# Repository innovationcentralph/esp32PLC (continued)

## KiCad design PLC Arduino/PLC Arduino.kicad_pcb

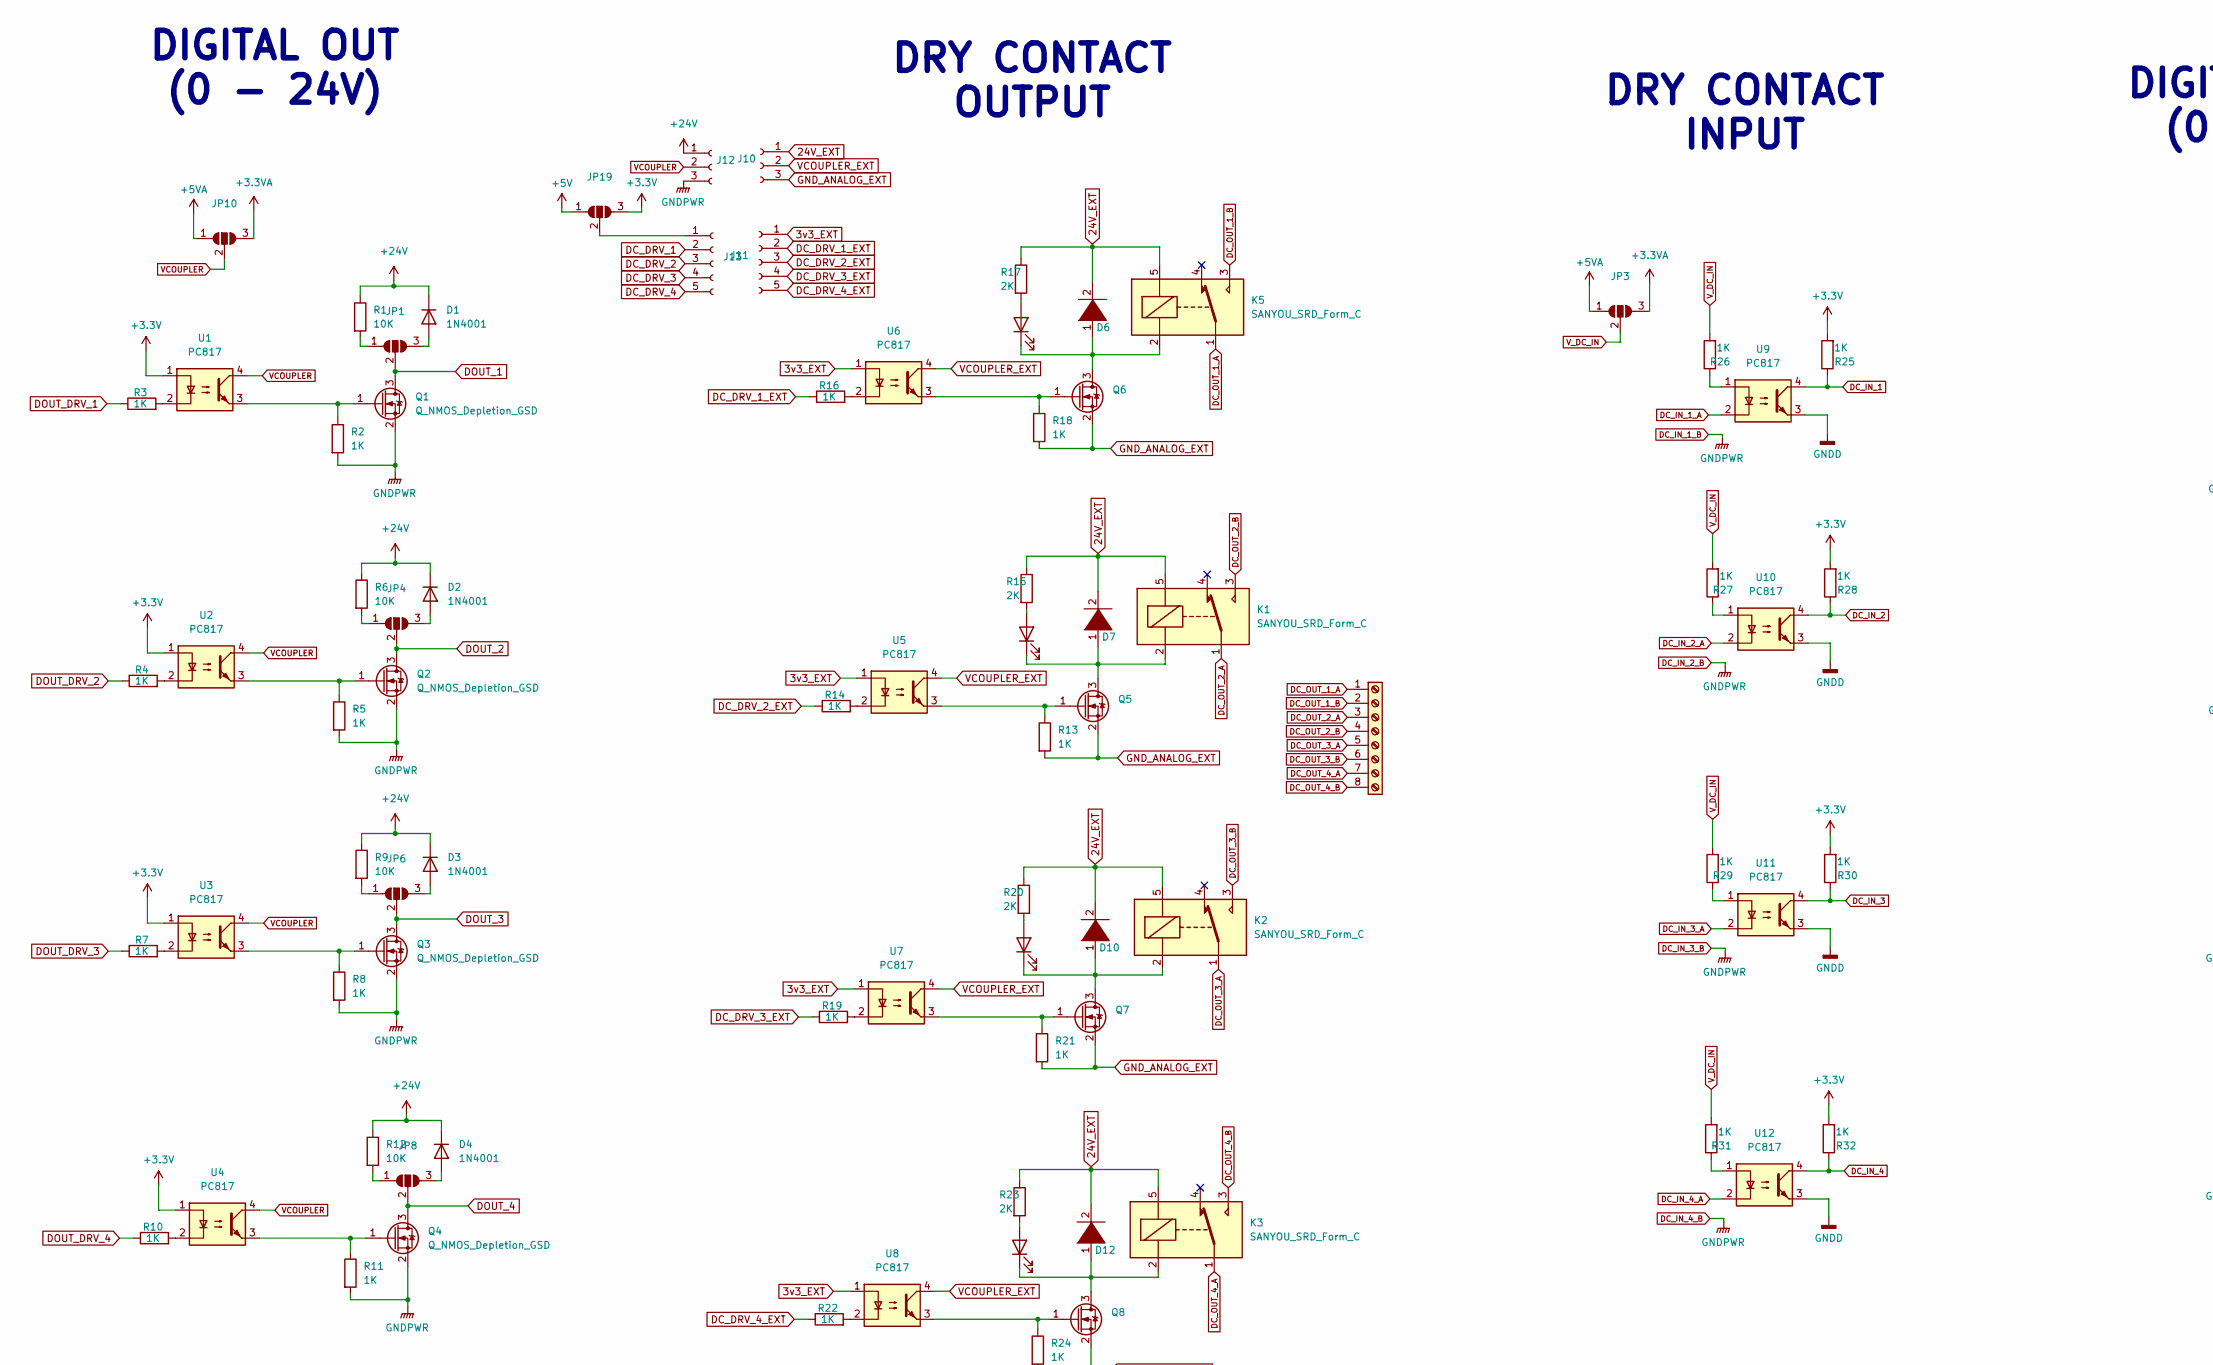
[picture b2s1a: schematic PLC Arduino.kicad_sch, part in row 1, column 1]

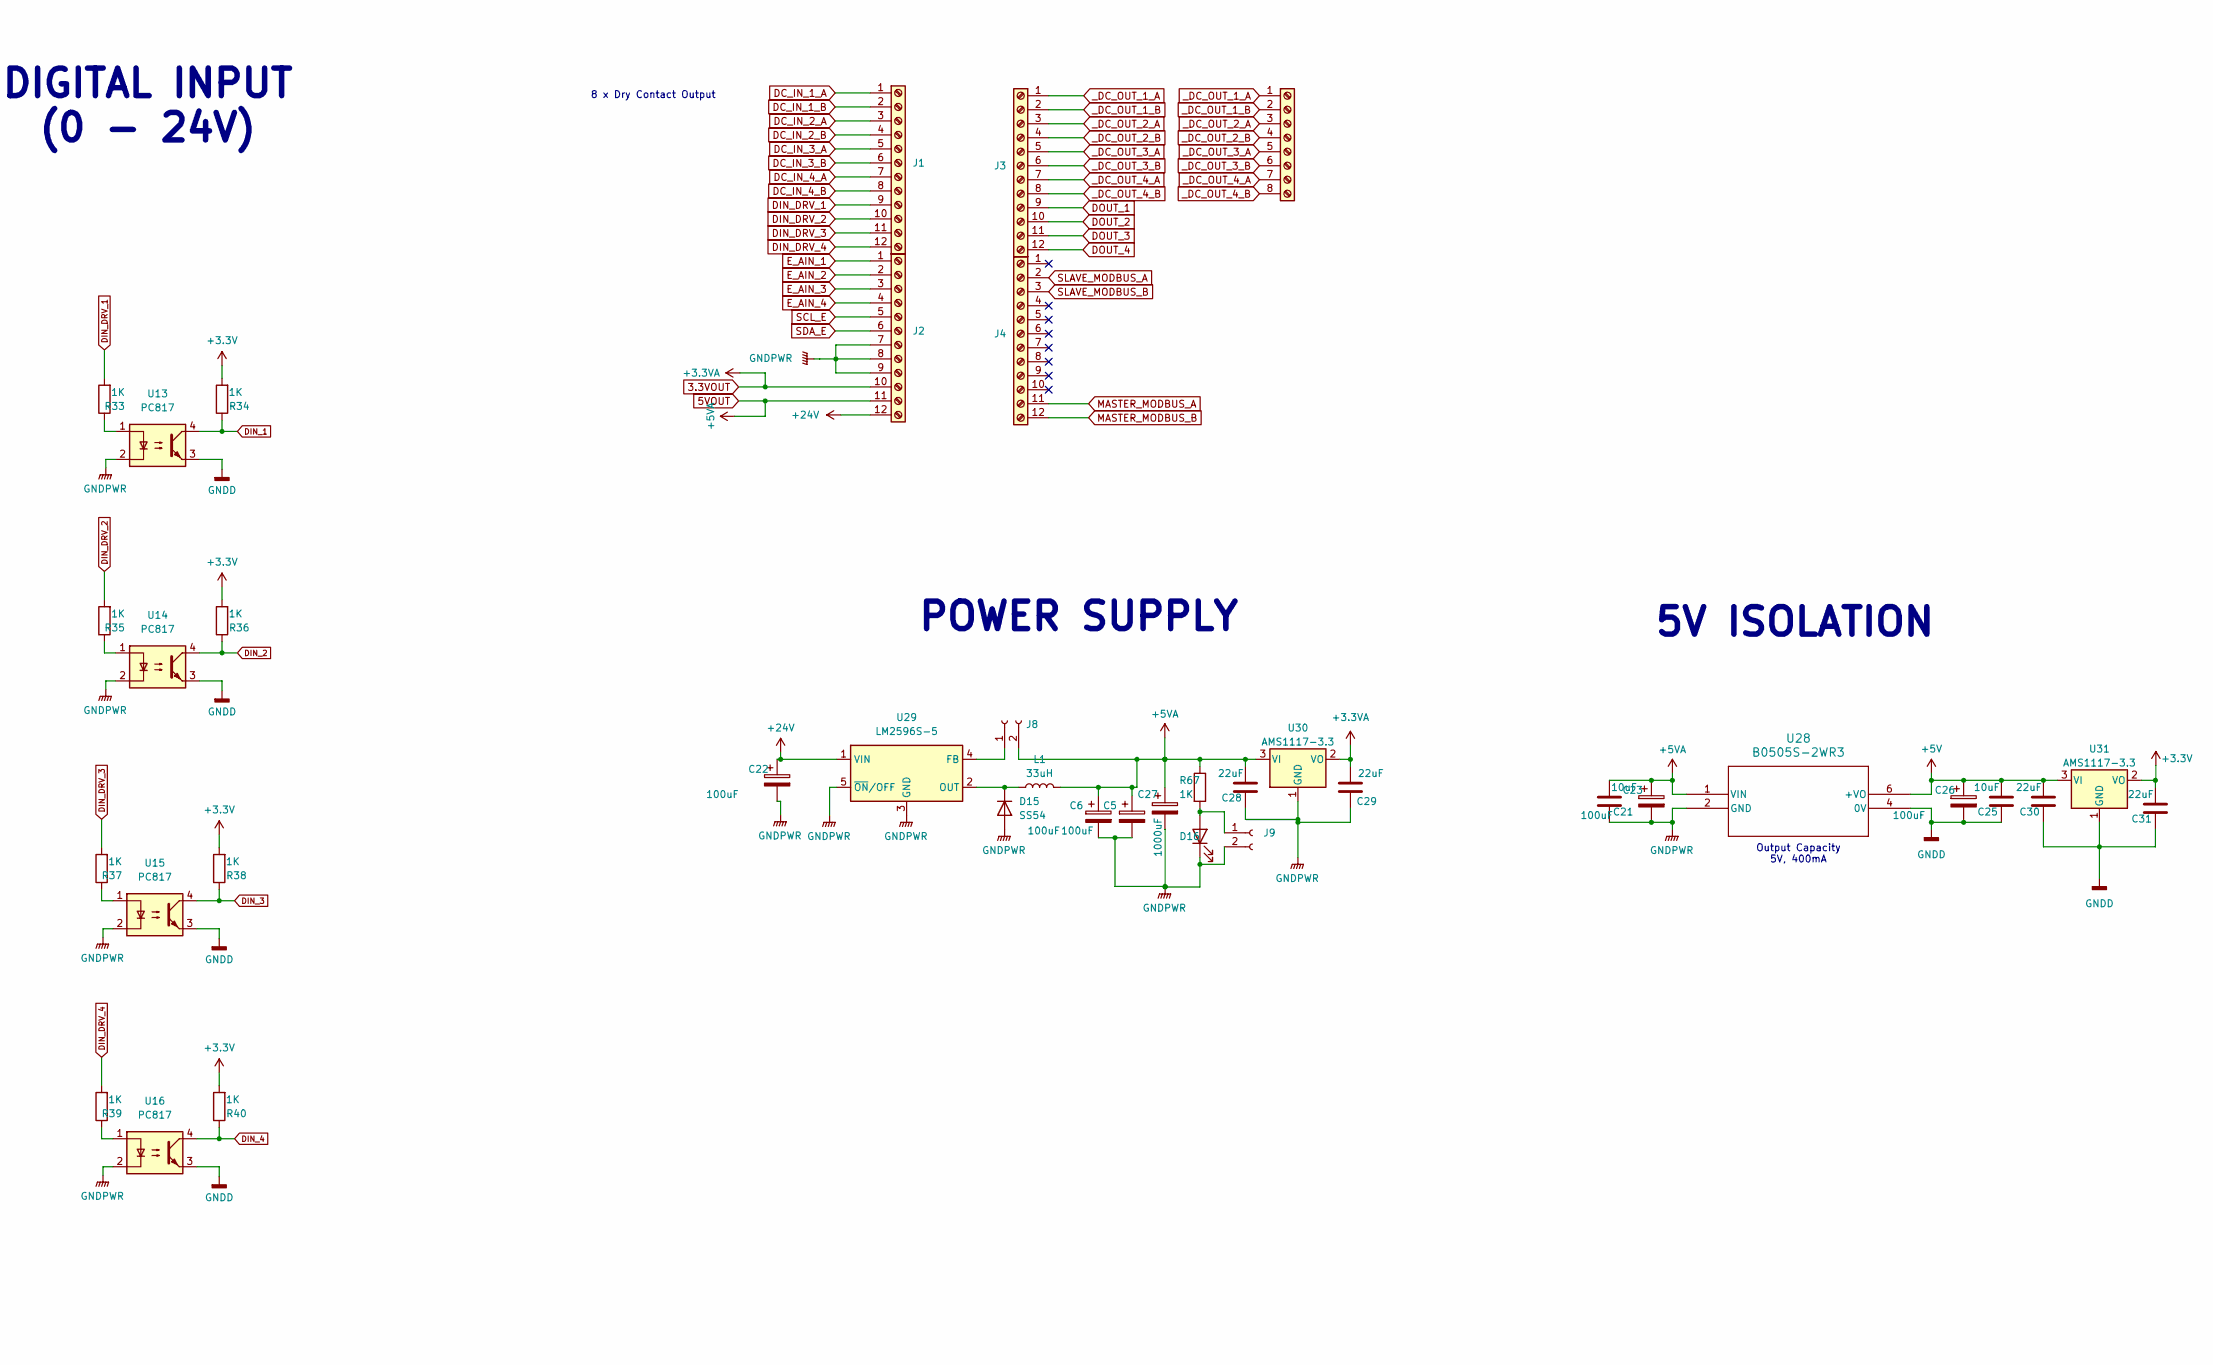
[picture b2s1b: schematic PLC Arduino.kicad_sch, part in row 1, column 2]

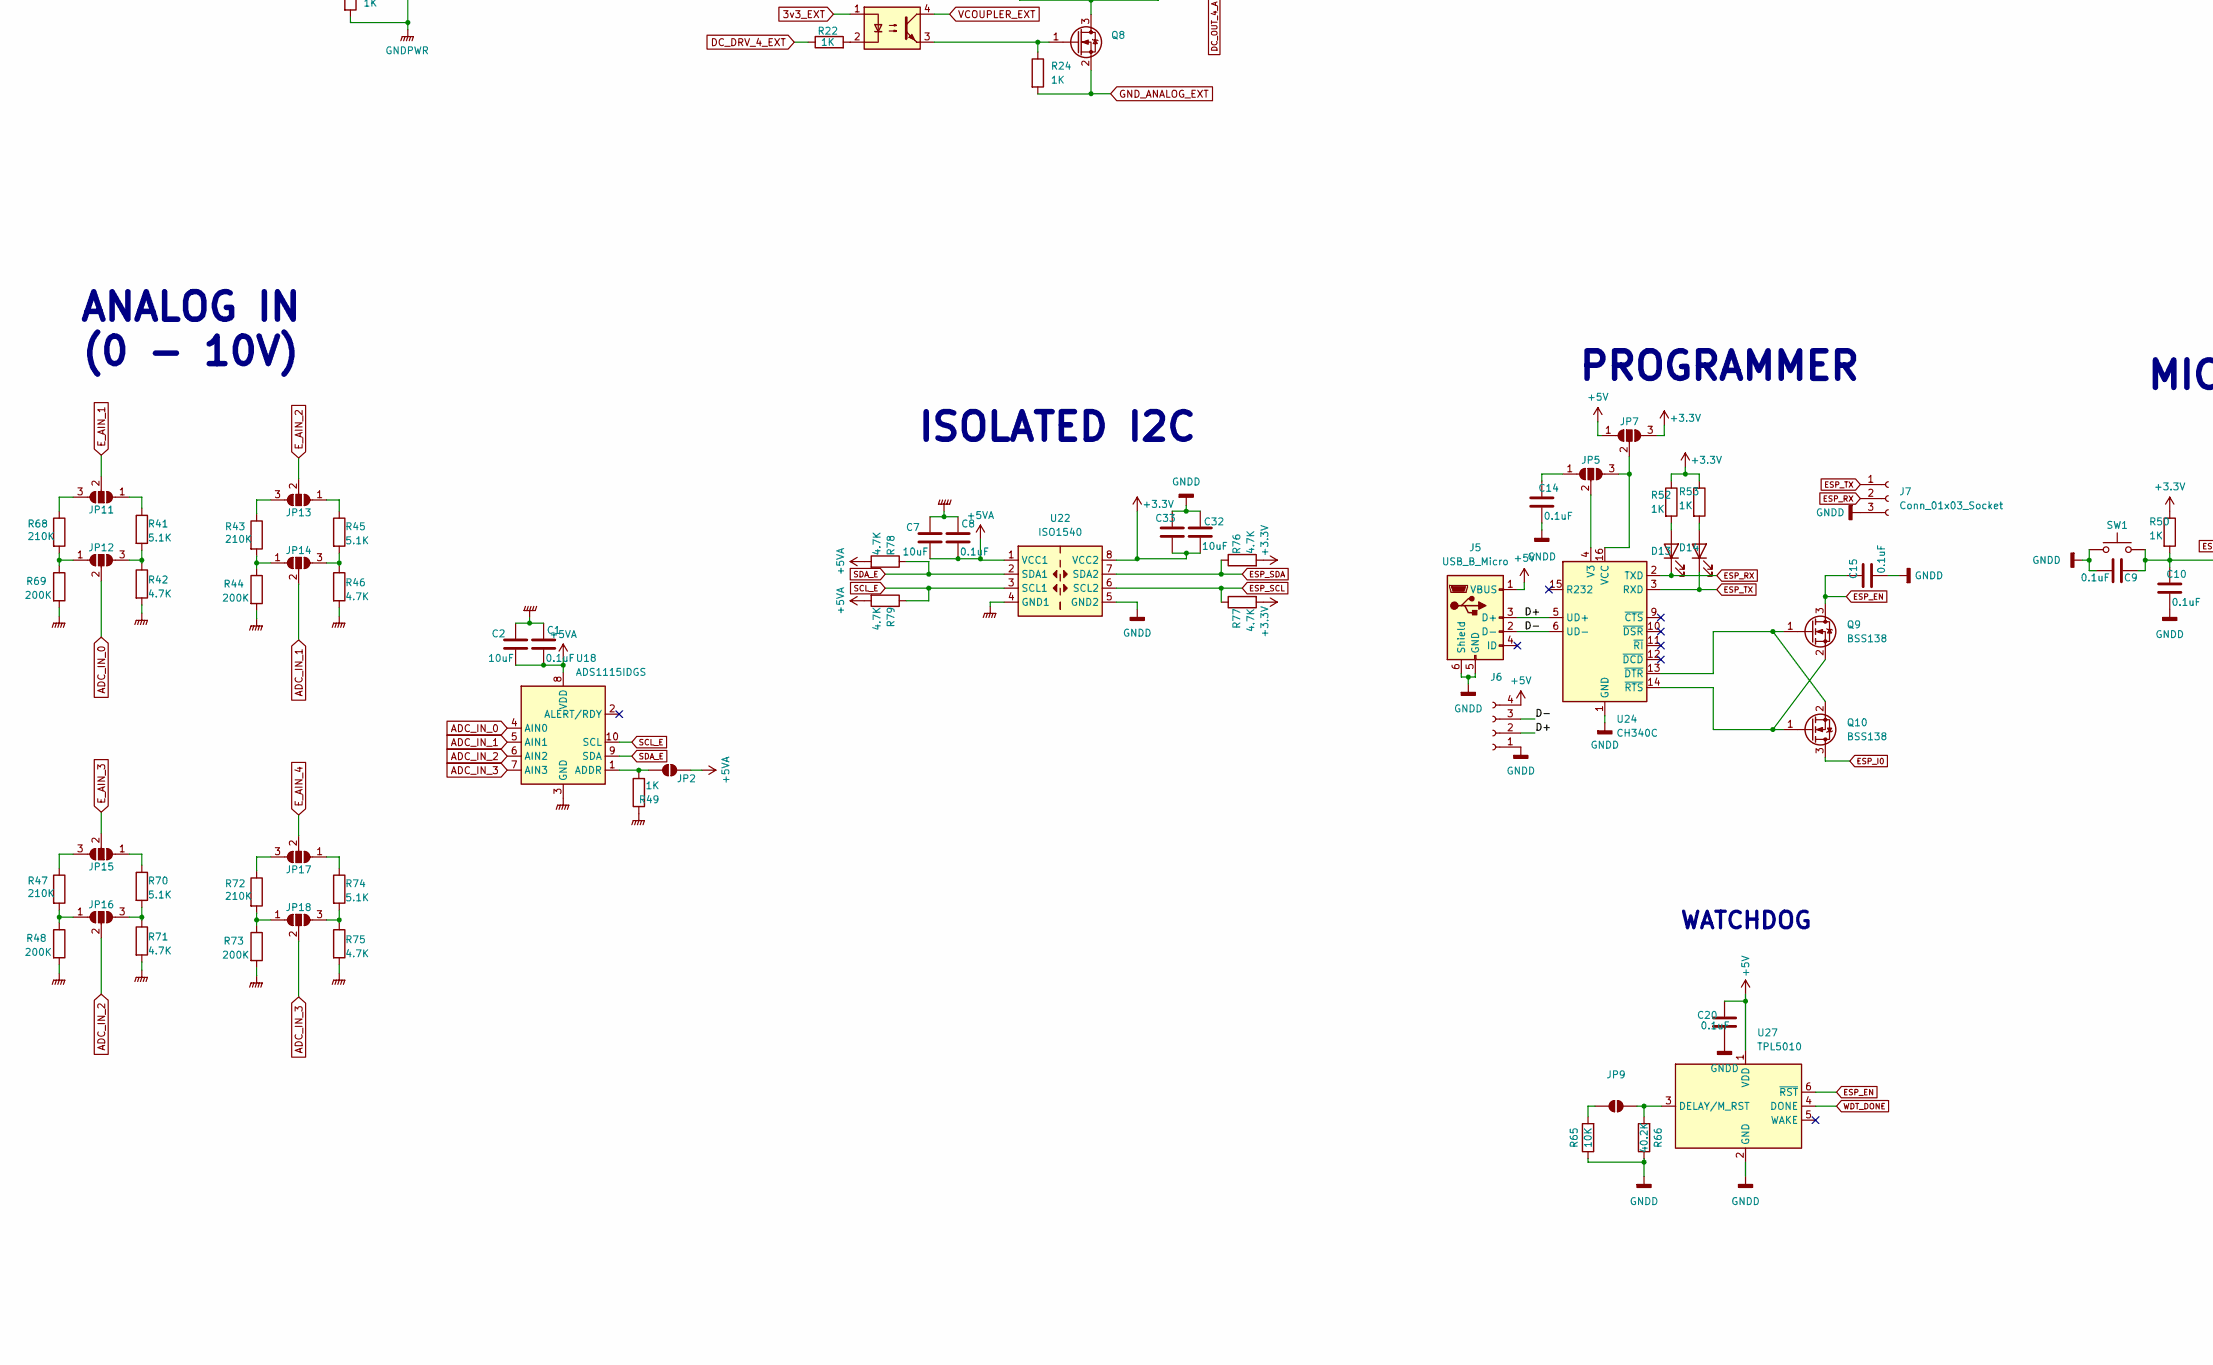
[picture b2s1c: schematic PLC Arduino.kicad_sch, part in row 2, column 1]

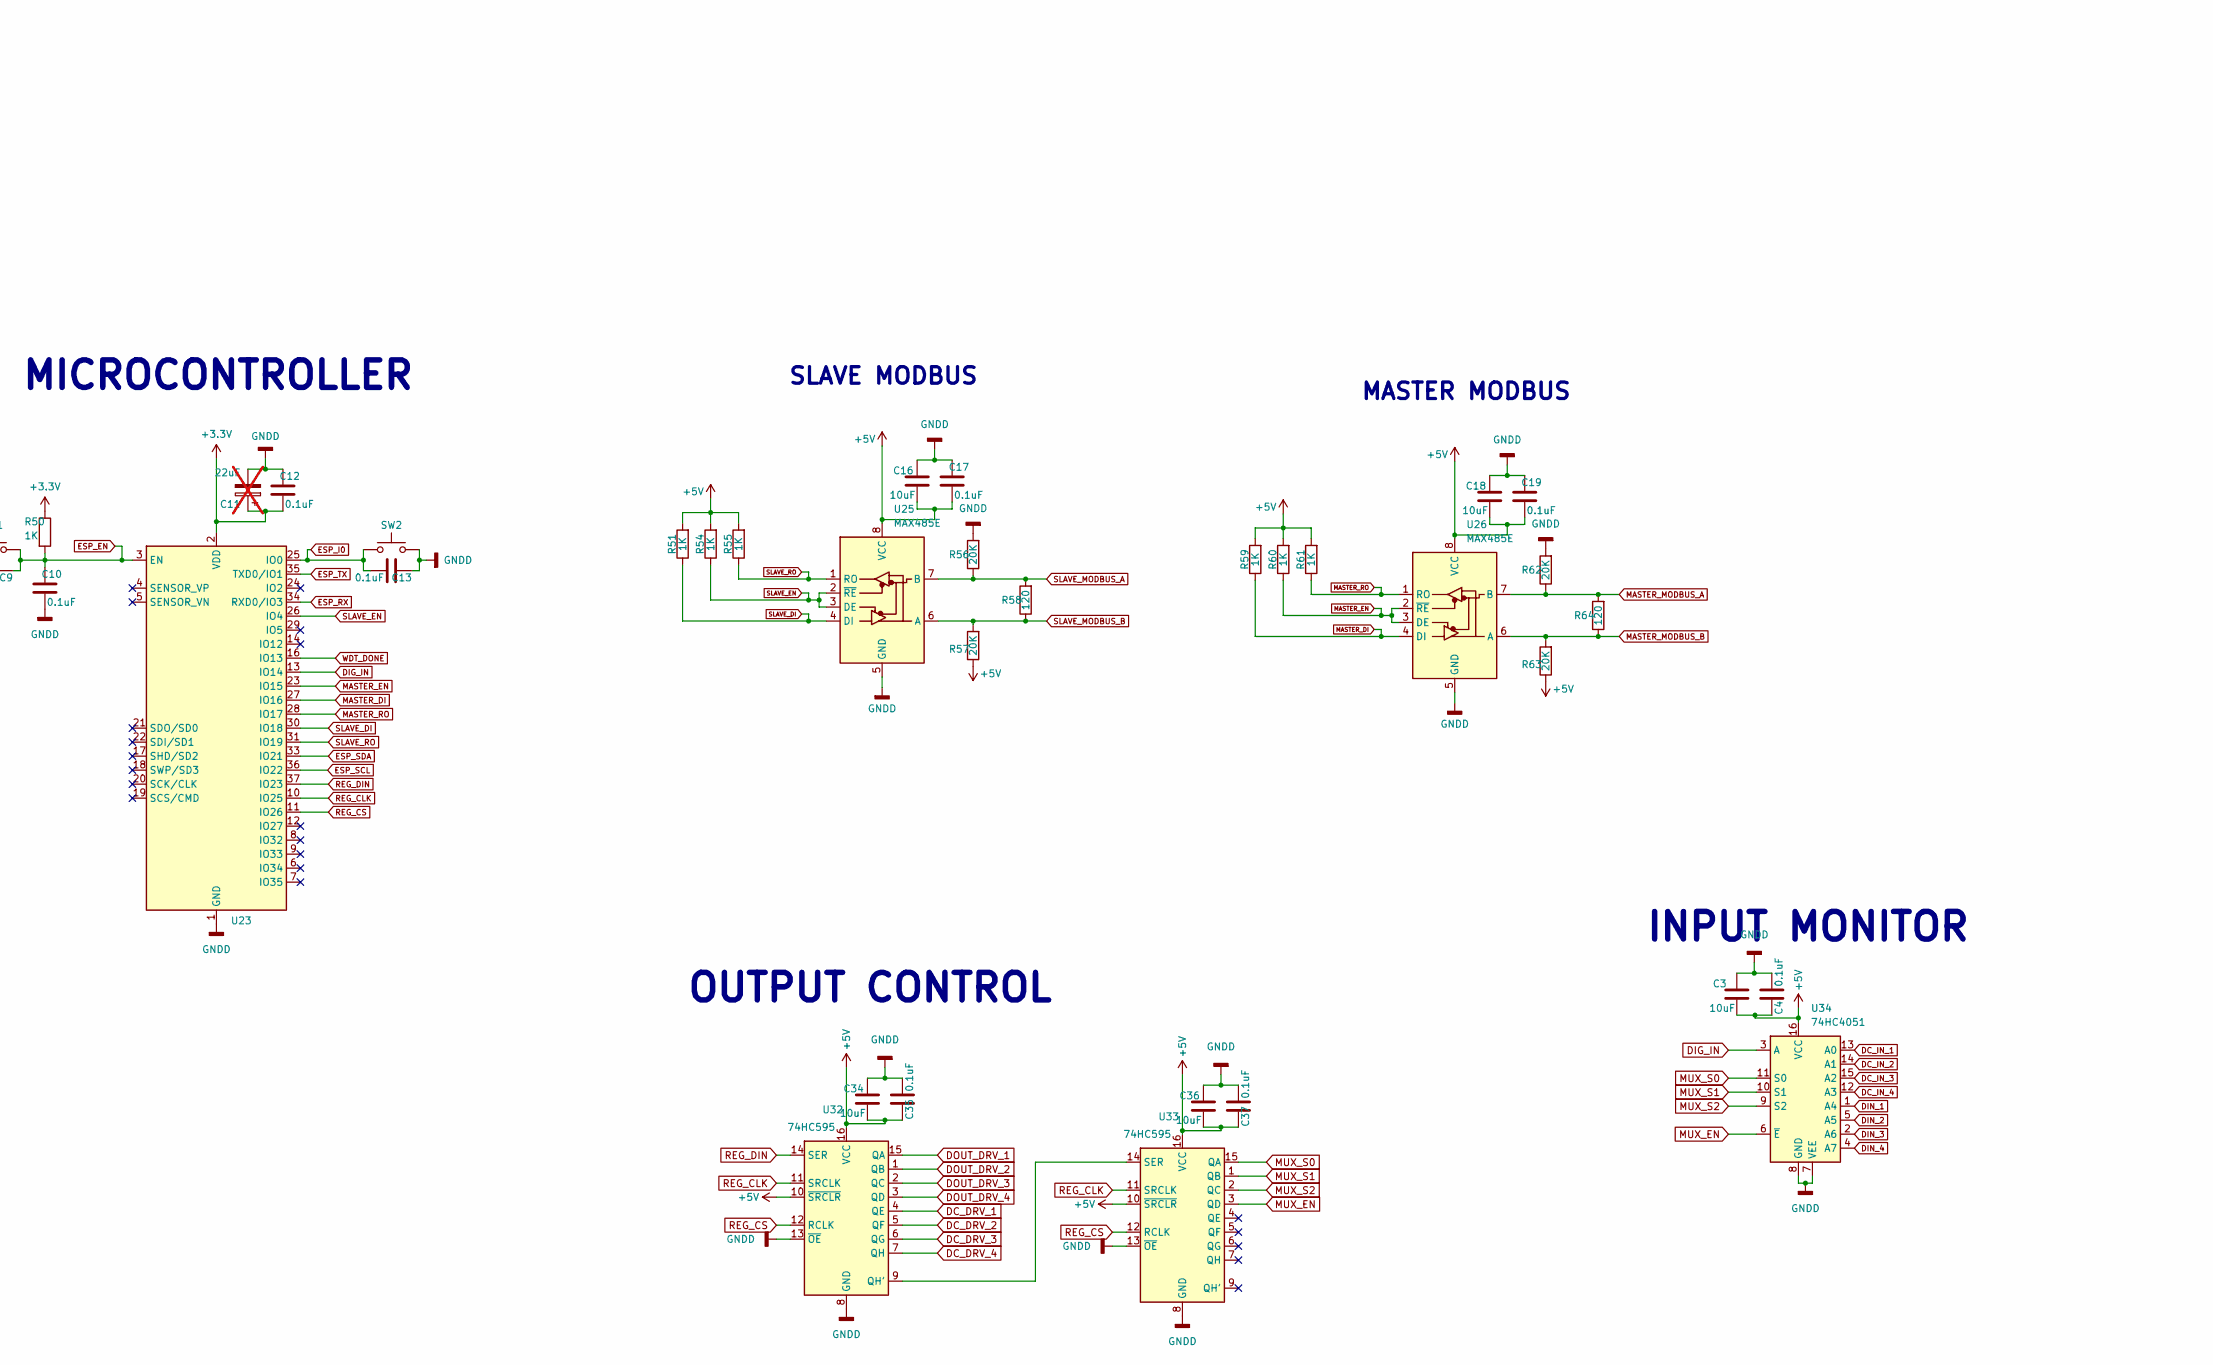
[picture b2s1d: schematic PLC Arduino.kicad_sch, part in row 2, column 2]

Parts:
C1, C4, C8, C9, C10, C12, C13, C14, C15, C17, C19, C20, C33, C35, C37: 0.1uF; C_0402_1005Metric; LCSC C60474
C2, C3, C7, C16, C18, C21, C25, C32, C34, C36: 10uF; C_0805_2012Metric_Pad1.18x1.45mm_HandSolder; LCSC C15850
C5, C6, C23, C26: 100uF; C_1210_3225Metric_Pad1.33x2.70mm_HandSolder; LCSC C394395
C11: 22uF; C_0603_1608Metric; LCSC C59461; not fitted
C22: 100uF; C_Elec_10x10.2; LCSC C28241
C27: 1000uF; C_Elec_10x10.2; LCSC C189257
C28, C29, C30, C31: 22uF; C_0603_1608Metric; LCSC C59461
D1, D2, D3, D4, D6, D7, D10, D12: 1N4001; D_SOD-123F; LCSC C2892326
D5, D8, D9, D11, D13, D14, D16: LED; LED_0805_2012Metric_Pad1.15x1.40mm_HandSolder; LCSC C2297
D15: SS54; D_SMA; LCSC C22452
J1, J2, J3, J4: Screw_Terminal_01x12; TerminalBlock_Phoenix_MKDS-1,5-12-5.08_1x12_P5.08mm_Horizon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
J5: USB_B_Micro; USB_Micro-B_Molex-105017-0001; LCSC C2972784
J6: Conn_01x04_Socket; JST_EH_B4B-EH-A_1x04_P2.50mm_Vertical
J7: Conn_01x03_Socket; JST_EH_B3B-EH-A_1x03_P2.50mm_Vertical
J8: Conn_01x02_Socket; PinHeader_1x02_P2.54mm_Vertical
J9: Conn_01x02_Socket; JST_EH_B2B-EH-A_1x02_P2.50mm_Vertical
J10, J12: Conn_01x03_Socket; PinHeader_1x03_P2.54mm_Vertical
J11, J13: Conn_01x05_Socket; PinHeader_1x05_P2.54mm_Vertical
J14, J15: Screw_Terminal_01x08; TerminalBlock_bornier-8_P5.08mm
JP1, JP3, JP4, JP5, JP6, JP7, JP8, JP10, JP11, JP12, JP13, JP14, JP15, JP16, JP17, JP18, JP19: SolderJumper_3_Open; SolderJumper-3_P1.3mm_Open_Pad1.0x1.5mm
JP2, JP9: SolderJumper_2_Open; SolderJumper-2_P1.3mm_Open_Pad1.0x1.5mm
K1, K2, K3, K5: SANYOU_SRD_Form_C; Relay_SPDT_SANYOU_SRD_Series_Form_C; LCSC C15840
L1: 33uH; L_Chilisin_BMRF00101040; LCSC C408490
Q1, Q2, Q3, Q4, Q5, Q6, Q7, Q8: Q_NMOS_Depletion_GSD; SOT-23-3; LCSC C75882
Q9, Q10: BSS138; SOT-23; LCSC C426569
R1, R6, R9, R12, R65: 10K; R_0603_1608Metric_Pad0.98x0.95mm_HandSolder; LCSC C25804
R2, R3, R4, R5, R7, R8, R10, R11, R13, R14, R16, R18, R19, R21, R22, R24, R25, R26, R27, R28, R29, R30, R31, R32, R33, R34, R35, R36, R37, R38, R39, R40, R49, R50, R51, R52, R53, R54, R55, R59, R60, R61, R67: 1K; R_0603_1608Metric_Pad0.98x0.95mm_HandSolder; LCSC C21190
R15, R17, R20, R23: 2K; R_0603_1608Metric_Pad0.98x0.95mm_HandSolder; LCSC C22975
R41, R45, R70, R74: 5.1K; R_0402_1005Metric_Pad0.72x0.64mm_HandSolder; LCSC C25905
R42, R46, R71, R75, R76, R77, R78, R79: 4.7K; R_0402_1005Metric_Pad0.72x0.64mm_HandSolder; LCSC C25900
R43, R47, R68, R72: 210K; R_0402_1005Metric_Pad0.72x0.64mm_HandSolder; LCSC C2686484
R44, R48, R69, R73: 200K; R_0402_1005Metric_Pad0.72x0.64mm_HandSolder; LCSC C286555
R56, R57, R62, R63: 20K; R_0805_2012Metric_Pad1.20x1.40mm_HandSolder; LCSC C163978
R58, R64: 120; R_0805_2012Metric_Pad1.20x1.40mm_HandSolder; LCSC C2907224
R66: 40.2K; R_0603_1608Metric_Pad0.98x0.95mm_HandSolder; LCSC C12447
SW1, SW2: SW_Push; SW_SPST_CK_RS282G05A3; LCSC C2689642
U1, U2, U3, U4, U5, U6, U7, U8, U9, U10, U11, U12, U13, U14, U15, U16: PC817; APC-817xx-SL_AMB; LCSC C66405
U18: ADS1115IDGS; DGS0010A_L; LCSC C37593
U22: ISO1540; SOIC-8_3.9x4.9mm_P1.27mm; LCSC C179739
U23: ESP32-WROOM-32; LCSC C529577
U24: CH340C; SOP-16_3.9x9.9mm_P1.27mm; LCSC C84681
U25, U26: MAX485E; SOP-8_3.9x4.9mm_P1.27mm; LCSC C481667
U27: TPL5010; SOT-23-6; LCSC C473912
U28: B0505S-2WR3; B_S-2WR2_MNS; LCSC C5369473
U29: LM2596S-5; TO-263-5_TabPin3; LCSC C347421
U30, U31: AMS1117-3.3; SOT-223-3_TabPin2; LCSC C5199435
U32, U33: 74HC595; SOIC-16_3.9x9.9mm_P1.27mm; LCSC C5947
U34: 74HC4051; SO-16_3.9x9.9mm_P1.27mm; LCSC C9386

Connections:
3.3VOUT: C29.2, J2.10, JP3.3 (B), JP10.3 (B), U30.2 (VO)
3v3_EXT: J11.1, U5.1, U6.1, U7.1, U8.1
5VOUT: C1.1, C2.2, C5.1, C6.1, C7.2, C8.1, C21.2, C23.1, C27.1, C28.2, J2.11, J8.2, JP2.2 (B), JP3.1 (A), JP10.1 (A), L1.2, R67.1, R78.2, R79.2, U18.8 (VDD), U22.1 (VCC1), U28.1 (VIN), U30.3 (VI)
24V_EXT: D6.2 (A), D7.2 (A), D10.2 (A), D12.2 (A), J10.1, K1.5, K2.5, K3.5, K5.5, R15.1, R17.1, R20.1, R23.1
+3.3V: C11.1, C12.1, C31.2, C32.2, C33.1, JP7.3 (B), JP19.3 (B), R25.2, R28.2, R30.2, R32.2, R34.2, R36.2, R38.2, R40.2, R50.1, R52.1, R53.1, R76.2, R77.2, U1.1, U2.1, U3.1, U4.1, U22.8 (VCC2), U23.2 (VDD), U31.2 (VO)
+5V: C3.2, C4.2, C16.2, C17.1, C18.2, C19.1, C20.1, C25.2, C26.1, C30.2, C34.2, C35.2, C36.2, C37.2, J5.1 (VBUS), J6.4, JP7.1 (A), JP19.1 (A), R51.2, R54.2, R55.2, R57.1, R59.2, R60.2, R61.2, R63.1, U25.8 (VCC), U26.8 (VCC), U27.1 (VDD), U28.6 (+VO), U31.3 (VI), U32.10 (~SRCLR), U32.16 (VCC), U33.10 (~SRCLR), U33.16 (VCC), U34.16 (VCC)
+24V: C22.1, D1.1 (K), D2.1 (K), D3.1 (K), D4.1 (K), J2.12, J12.1, R1.1, R6.1, R9.1, R12.1, U29.1 (VIN)
/D+: J5.3 (D+), J6.2, U24.5 (UD+)
/D-: J5.2 (D-), J6.3, U24.6 (UD-)
ADC_IN_0: JP12.2 (C), U18.4 (AIN0)
ADC_IN_1: JP14.2 (C), U18.5 (AIN1)
ADC_IN_2: JP16.2 (C), U18.6 (AIN2)
ADC_IN_3: JP18.2 (C), U18.7 (AIN3)
DC_DRV_1: J13.2, U32.4 (QE)
DC_DRV_1_EXT: J11.2, R16.1
DC_DRV_2: J13.3, U32.5 (QF)
DC_DRV_2_EXT: J11.3, R14.1
DC_DRV_3: J13.4, U32.6 (QG)
DC_DRV_3_EXT: J11.4, R19.1
DC_DRV_4: J13.5, U32.7 (QH)
DC_DRV_4_EXT: J11.5, R22.1
DC_IN_1: R25.1, U9.4, U34.13 (A0)
DC_IN_1_A: J1.1, U9.2
DC_IN_1_B: C1.2, C2.1, C5.2, C6.2, C7.1, C8.2, C21.1, C22.2, C23.2, C27.2, C28.1, C29.1, D15.2 (A), D16.1 (K), J1.2, J1.4, J1.6, J1.8, J2.7, J2.8, J2.9, J9.2, J12.3, Q1.2 (S), Q2.2 (S), Q3.2 (S), Q4.2 (S), R2.2, R5.2, R8.2, R11.2, R42.2, R44.2, R46.2, R48.2, R49.1, R69.2, R71.2, R73.2, R75.2, U13.2, U14.2, U15.2, U16.2, U18.3 (GND), U22.4 (GND1), U28.2 (GND), U29.3 (GND), U29.5 (~ON/OFF), U30.1 (GND)
DC_IN_2: R28.1, U10.4, U34.14 (A1)
DC_IN_2_A: J1.3, U10.2
DC_IN_3: R30.1, U11.4, U34.15 (A2)
DC_IN_3_A: J1.5, U11.2
DC_IN_4: R32.1, U12.4, U34.12 (A3)
DC_IN_4_A: J1.7, U12.2
DC_OUT_1_A: J14.1, K5.1
DC_OUT_1_B: J14.2, K5.3
DC_OUT_2_A: J14.3, K1.1
DC_OUT_2_B: J14.4, K1.3
DC_OUT_3_A: J14.5, K2.1
DC_OUT_3_B: J14.6, K2.3
DC_OUT_4_A: J14.7, K3.1
DC_OUT_4_B: J14.8, K3.3
DIG_IN: U23.13 (IO14), U34.3 (A)
DIN_1: R34.1, U13.4, U34.1 (A4)
DIN_2: R36.1, U14.4, U34.5 (A5)
DIN_3: R38.1, U15.4, U34.2 (A6)
DIN_4: R40.1, U16.4, U34.4 (A7)
DIN_DRV_1: J1.9, R33.2
DIN_DRV_2: J1.10, R35.2
DIN_DRV_3: J1.11, R37.2
DIN_DRV_4: J1.12, R39.2
DOUT_1: J3.9, JP1.2 (C), Q1.3 (D)
DOUT_2: J3.10, JP4.2 (C), Q2.3 (D)
DOUT_3: J3.11, JP6.2 (C), Q3.3 (D)
DOUT_4: J3.12, JP8.2 (C), Q4.3 (D)
DOUT_DRV_1: R3.1, U32.15 (QA)
DOUT_DRV_2: R4.1, U32.1 (QB)
DOUT_DRV_3: R7.1, U32.2 (QC)
DOUT_DRV_4: R10.1, U32.3 (QD)
ESP_EN: C9.2, C10.2, C15.2, Q9.3 (D), R50.2, SW1.2, U23.3 (EN), U27.6 (~RST)
ESP_I0: C13.1, Q10.3 (D), SW2.1, U23.25 (IO0)
ESP_RX: D13.1 (K), J7.2, U23.34 (RXD0/IO3), U24.2 (TXD)
ESP_SCL: R77.1, U22.6 (SCL2), U23.36 (IO22)
ESP_SDA: R76.1, U22.7 (SDA2), U23.33 (IO21)
ESP_TX: D14.1 (K), J7.1, U23.35 (TXD0/IO1), U24.3 (RXD)
E_AIN_1: J2.1, JP11.2 (C)
E_AIN_2: J2.2, JP13.2 (C)
E_AIN_3: J2.3, JP15.2 (C)
E_AIN_4: J2.4, JP17.2 (C)
GNDD: C3.1, C4.1, C9.1, C10.1, C11.2, C12.2, C13.2, C14.1, C15.1, C16.1, C17.2, C18.1, C19.2, C20.2, C25.1, C26.2, C30.1, C31.1, C32.1, C33.2, C34.1, C35.1, C36.1, C37.1, J5.5 (GND), J5.6 (Shield), J6.1, J7.3, R56.2, R62.2, R65.1, R66.1, SW1.1, SW2.2, U9.3, U10.3, U11.3, U12.3, U13.3, U14.3, U15.3, U16.3, U22.5 (GND2), U23.1 (GND), U23.15 (GND), U23.38 (GND), U23.39 (GND), U24.1 (GND), U25.5 (GND), U26.5 (GND), U27.2 (GND), U28.4 (0V), U31.1 (GND), U32.8 (GND), U32.13 (~OE), U33.8 (GND), U33.13 (~OE), U34.7 (VEE), U34.8 (GND)
GND_ANALOG_EXT: J10.3, Q5.2 (S), Q6.2 (S), Q7.2 (S), Q8.2 (S), R13.2, R18.2, R21.2, R24.2
MASTER_DI: R59.1, U23.27 (IO16), U26.4 (DI)
MASTER_EN: R60.1, U23.23 (IO15), U26.2 (~RE), U26.3 (DE)
MASTER_MODBUS_A: J4.11, R62.1, R64.2, U26.7 (B)
MASTER_MODBUS_B: J4.12, R63.2, R64.1, U26.6 (A)
MASTER_RO: R61.1, U23.28 (IO17), U26.1 (RO)
MUX_EN: U33.3 (QD), U34.6 (~E)
MUX_S0: U33.15 (QA), U34.11 (S0)
MUX_S1: U33.1 (QB), U34.10 (S1)
MUX_S2: U33.2 (QC), U34.9 (S2)
unnamed: D1.2 (A), JP1.3 (B)
unnamed: D2.2 (A), JP4.3 (B)
unnamed: D3.2 (A), JP6.3 (B)
unnamed: D4.2 (A), JP8.3 (B)
unnamed: D5.2 (A), R17.2
unnamed: D5.1 (K), D6.1 (K), K5.2, Q6.3 (D)
unnamed: D7.1 (K), D8.1 (K), K1.2, Q5.3 (D)
unnamed: D8.2 (A), R15.2
unnamed: D9.2 (A), R20.2
unnamed: D9.1 (K), D10.1 (K), K2.2, Q7.3 (D)
unnamed: D11.2 (A), R23.2
unnamed: D11.1 (K), D12.1 (K), K3.2, Q8.3 (D)
unnamed: D13.2 (A), R52.2
unnamed: D14.2 (A), R53.2
unnamed: D15.1 (K), L1.1, U29.2 (OUT)
unnamed: D16.2 (A), J9.1, R67.2
unnamed: J8.1, U29.4 (FB)
unnamed: J13.1, JP19.2 (C)
unnamed: JP1.1 (A), R1.2
unnamed: JP2.1 (A), R49.2, U18.1 (ADDR)
unnamed: JP4.1 (A), R6.2
unnamed: C14.2, JP5.1 (A)
unnamed: JP5.3 (B), JP7.2 (C), U24.16 (VCC)
unnamed: JP5.2 (C), U24.4 (V3)
unnamed: JP6.1 (A), R9.2
unnamed: JP8.1 (A), R12.2
unnamed: JP9.1 (A), R65.2
unnamed: JP9.2 (B), R66.2, U27.3 (DELAY/M_RST)
unnamed: JP11.1 (A), R41.1
unnamed: JP11.3 (B), R68.1
unnamed: JP12.1 (A), R68.2, R69.1
unnamed: JP12.3 (B), R41.2, R42.1
unnamed: JP13.1 (A), R45.1
unnamed: JP13.3 (B), R43.1
unnamed: JP14.1 (A), R43.2, R44.1
unnamed: JP14.3 (B), R45.2, R46.1
unnamed: JP15.1 (A), R70.1
unnamed: JP15.3 (B), R47.1
unnamed: JP16.1 (A), R47.2, R48.1
unnamed: JP16.3 (B), R70.2, R71.1
unnamed: JP17.1 (A), R74.1
unnamed: JP17.3 (B), R72.1
unnamed: JP18.1 (A), R72.2, R73.1
unnamed: JP18.3 (B), R74.2, R75.1
unnamed: Q1.1 (G), R2.1, U1.3
unnamed: Q2.1 (G), R5.1, U2.3
unnamed: Q3.1 (G), R8.1, U3.3
unnamed: Q4.1 (G), R11.1, U4.3
unnamed: Q5.1 (G), R13.1, U5.3
unnamed: Q6.1 (G), R18.1, U6.3
unnamed: Q7.1 (G), R21.1, U7.3
unnamed: Q8.1 (G), R24.1, U8.3
unnamed: Q9.2 (S), Q10.1 (G), U24.14 (~RTS)
unnamed: Q9.1 (G), Q10.2 (S), U24.13 (~DTR)
unnamed: R3.2, U1.2
unnamed: R4.2, U2.2
unnamed: R7.2, U3.2
unnamed: R10.2, U4.2
unnamed: R14.2, U5.2
unnamed: R16.2, U6.2
unnamed: R19.2, U7.2
unnamed: R22.2, U8.2
unnamed: R26.1, U9.1
unnamed: R27.1, U10.1
unnamed: R29.1, U11.1
unnamed: R31.1, U12.1
unnamed: R33.1, U13.1
unnamed: R35.1, U14.1
unnamed: R37.1, U15.1
unnamed: R39.1, U16.1
unnamed: U32.9 (QH'), U33.14 (SER)
REG_CLK: U23.10 (IO25), U32.11 (SRCLK), U33.11 (SRCLK)
REG_CS: U23.11 (IO26), U32.12 (RCLK), U33.12 (RCLK)
REG_DIN: U23.37 (IO23), U32.14 (SER)
SCL_E: J2.5, R79.1, U18.10 (SCL), U22.3 (SCL1)
SDA_E: J2.6, R78.1, U18.9 (SDA), U22.2 (SDA1)
SLAVE_DI: R51.1, U23.30 (IO18), U25.4 (DI)
SLAVE_EN: R54.1, U23.26 (IO4), U25.2 (~RE), U25.3 (DE)
SLAVE_MODBUS_A: J4.2, R56.1, R58.2, U25.7 (B)
SLAVE_MODBUS_B: J4.3, R57.2, R58.1, U25.6 (A)
SLAVE_RO: R55.1, U23.31 (IO19), U25.1 (RO)
VCOUPLER: J12.2, JP10.2 (C), U1.4, U2.4, U3.4, U4.4
VCOUPLER_EXT: J10.2, U5.4, U6.4, U7.4, U8.4
V_DC_IN: JP3.2 (C), R26.2, R27.2, R29.2, R31.2
WDT_DONE: U23.16 (IO13), U27.4 (DONE)
_DC_OUT_1_A: J3.1, J15.1
_DC_OUT_1_B: J3.2, J15.2
_DC_OUT_2_A: J3.3, J15.3
_DC_OUT_2_B: J3.4, J15.4
_DC_OUT_3_A: J3.5, J15.5
_DC_OUT_3_B: J3.6, J15.6
_DC_OUT_4_A: J3.7, J15.7
_DC_OUT_4_B: J3.8, J15.8

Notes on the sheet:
WATCHDOG
Output Capacity 5V, 400mA
5V ISOLATION
INPUT MONITOR
DRY CONTACT OUTPUT
MASTER MODBUS
SLAVE MODBUS
POWER SUPPLY
PROGRAMMER
8 x Dry Contact Output
MICROCONTROLLER
ANALOG IN (0 - 10V)
DIGITAL OUT (0 - 24V)
ISOLATED I2C
OUTPUT CONTROL
DRY CONTACT INPUT
DIGITAL INPUT (0 - 24V)

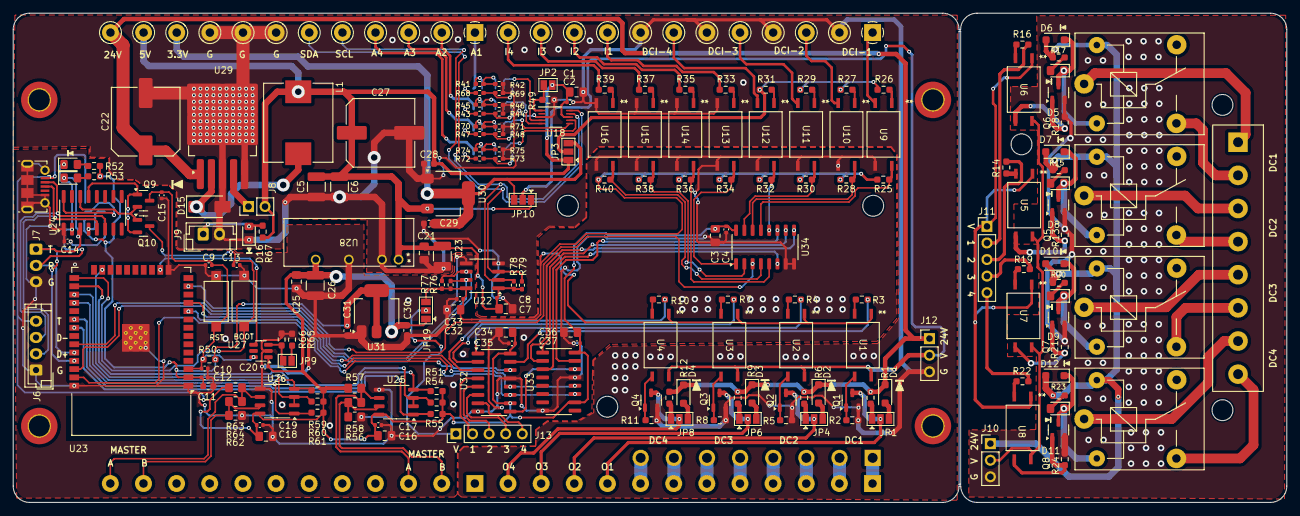
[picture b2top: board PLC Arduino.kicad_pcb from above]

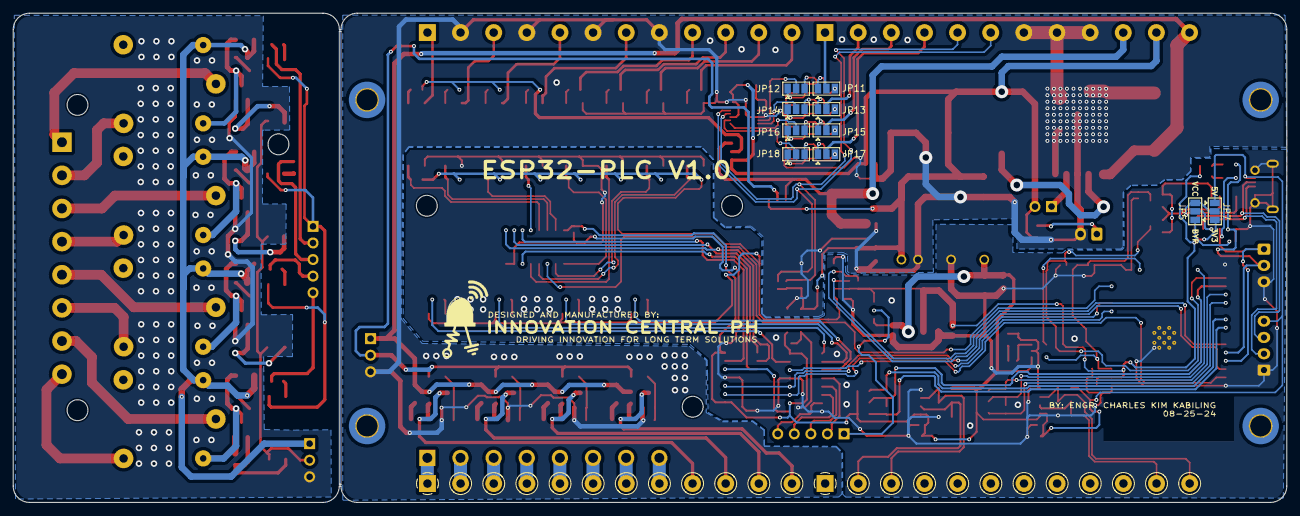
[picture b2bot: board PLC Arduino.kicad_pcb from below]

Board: 2 copper layers, 195.2 x 75.0 mm, 212 parts (12 on the bottom side), 169 nets.

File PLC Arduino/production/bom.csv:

Designator,Footprint,Quantity,Value,LCSC Part #
"C1, C10, C12, C13, C14, C15, C17, C19, C20, C33, C35, C37, C4, C8, C9",0402,15,0.1uF, C60474
"C11, C28, C29, C30, C31",0603,5,22uF, C59461
"C16, C18, C2, C21, C25, C3, C32, C34, C36, C7",0805,10,10uF,C15850
C22,C_Elec_10x10.2,1,100uF, C28241
"C23, C26, C5, C6",1210,4,100uF,C394395 
C27,C_Elec_10x10.2,1,1000uF, C189257
"D1, D10, D12, D2, D3, D4, D6, D7",D_SOD-123F,8,1N4001,C2892326
"D11, D13, D14, D16, D5, D8, D9",0805,7,LED,C2297
D15,D_SMA,1,SS54,C22452
"J1, J2, J3, J4","TerminalBlock_Phoenix_MKDS-1,5-12-5.08_1x12_P5.08mm_Horizontal",4,Screw_Terminal_01x12,
"J10, J12",PinHeader_1x03_P2.54mm_Vertical,2,Conn_01x03_Socket,
"J11, J13",PinHeader_1x05_P2.54mm_Vertical,2,Conn_01x05_Socket,
"J14, J15",TerminalBlock_bornier-8_P5.08mm,2,Screw_Terminal_01x08,
J5,USB_Micro-B_Molex-105017-0001,1,USB_B_Micro,C2972784
J6,JST_EH_B4B-EH-A_1x04_P2.50mm_Vertical,1,Conn_01x04_Socket,
J7,JST_EH_B3B-EH-A_1x03_P2.50mm_Vertical,1,Conn_01x03_Socket,
J8,PinHeader_1x02_P2.54mm_Vertical,1,Conn_01x02_Socket,
J9,JST_EH_B2B-EH-A_1x02_P2.50mm_Vertical,1,Conn_01x02_Socket,
"JP5, JP7",SolderJumper-3_P1.3mm_Open_Pad1.0x1.5mm,2,SolderJumper_3_Open,
JP9,SolderJumper-2_P1.3mm_Open_Pad1.0x1.5mm,1,SolderJumper_2_Open,
"K1, K2, K3, K5",Relay_SPDT_SANYOU_SRD_Series_Form_C,4,SANYOU_SRD_Form_C,C15840
L1,L_Chilisin_BMRF00101040,1,33uH,C408490
"Q1, Q2, Q3, Q4, Q5, Q6, Q7, Q8",SOT-23-3,8,Q_NMOS_Depletion_GSD, C75882
"Q10, Q9",SOT-23,2,BSS138,C426569
"R1, R12, R6, R65, R9",0603,5,10K,C25804
"R10, R11, R13, R14, R16, R18, R19, R2, R21, R22, R24, R25, R26, R27, R28, R29, R3, R30, R31, R32, R33, R34, R35, R36, R37, R38, R39, R4, R40, R49, R5, R50, R51, R52, R53, R54, R55, R59, R60, R61, R67, R7, R8",0603,43,1K,C21190
"R15, R17, R20, R23",0603,4,2K,C22975
"R41, R45, R70, R74",0402,4,5.1K, C25905
"R42, R46, R71, R75, R76, R77, R78, R79",0402,8,4.7K,C25900
"R43, R47, R68, R72",0402,4,210K,C2686484
"R44, R48, R69, R73",0402,4,200K,C286555
"R56, R57, R62, R63",0805,4,20K,C163978
"R58, R64",0805,2,120,C2907224
R66,0603,1,40.2K,C12447
"SW1, SW2",SW_SPST_CK_RS282G05A3,2,SW_Push,C2689642
"U1, U10, U11, U12, U13, U14, U15, U16, U2, U3, U4, U5, U6, U7, U8, U9",APC-817xx-SL_AMB,16,PC817,C66405
U18,DGS0010A_L,1,ADS1115IDGS,C37593
U22,SOIC-8_3.9x4.9mm_P1.27mm,1,ISO1540,C179739
U23,ESP32-WROOM-32,1,ESP32-WROOM-32,C529577
U24,SOP-16_3.9x9.9mm_P1.27mm,1,CH340C,C84681
"U25, U26",SOP-8_3.9x4.9mm_P1.27mm,2,MAX485E,C481667
U27,SOT-23-6,1,TPL5010,C473912
U28,B_S-2WR2_MNS,1,B0505S-2WR3,C5369473
U29,TO-263-5_TabPin3,1,LM2596S-5,C347421
"U30, U31",SOT-223-3_TabPin2,2,AMS1117-3.3,C5199435
"U32, U33",SOIC-16_3.9x9.9mm_P1.27mm,2,74HC595,C5947
U34,SO-16_3.9x9.9mm_P1.27mm,1,74HC4051, C9386
